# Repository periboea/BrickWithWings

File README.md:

# BrickWithWings

## What this thing is.

custom flight controller built around the STM32F446RETx microcontroller that currently has no wings and lives entirely rentfree in my head.

no specific target UAV in mind. primary purpose as a learning ground.

## Current status.

what exists: schematic of the power supply, microcontroller core, and ICM-42688-P motion sensor wired up with 0 ERC errors.

what will exist in the future (probably. hopefully): proper layout of components' footprints. routing. more features.

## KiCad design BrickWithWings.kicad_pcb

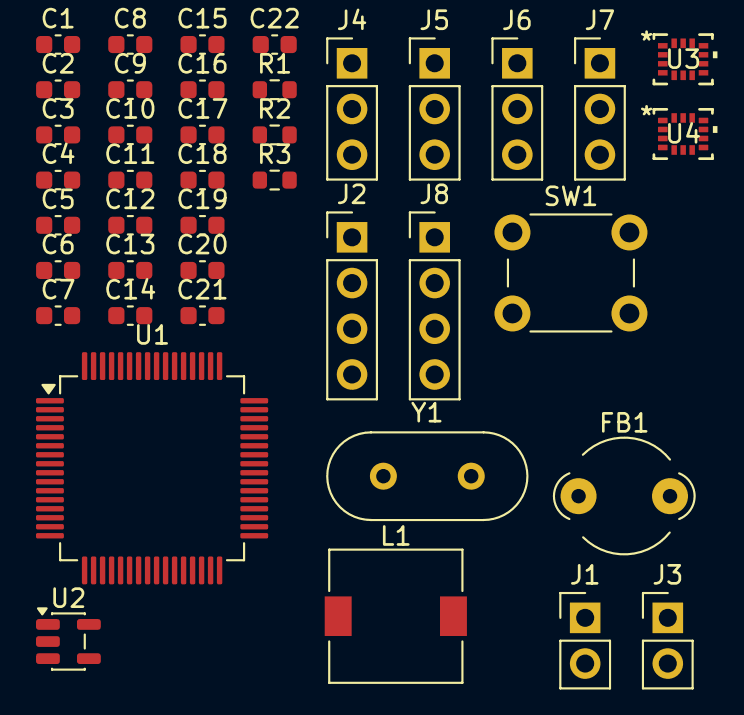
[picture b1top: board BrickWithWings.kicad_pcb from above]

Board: 2 copper layers, 41 parts (0 on the bottom side), 27 nets, no tracks yet.

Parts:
C1, C2, C3, C4, C6, C9, C15, C16: 100nF; C_0603_1608Metric
C5: 4.7uF; C_0603_1608Metric
C7, C12, C13: 1uF; C_0603_1608Metric
C8: 2.2muF; C_0603_1608Metric
C10, C11: 20pF; C_0603_1608Metric
C14: 10uF; C_0603_1608Metric
C17, C18: 22uF; C_0603_1608Metric
C19: 75pF; C_0603_1608Metric
C20: 0.1uF; C_0603_1608Metric
C21: 2.2uF; C_0603_1608Metric
C22: 10nF; C_0603_1608Metric
FB1: FerriteBead; LairdTech_28C0236-0JW-10
J1, J3: Conn_01x02_Pin; PinHeader_1x02_P2.54mm_Vertical
J2, J8: Conn_01x04_Pin; PinHeader_1x04_P2.54mm_Vertical
J4, J5, J6, J7: Conn_01x03_Pin; PinHeader_1x03_P2.54mm_Vertical
L1: 10uH; L_7.3x7.3_H4.5
R1: 10kΩ; R_0603_1608Metric
R2: 100kΩ; R_0603_1608Metric
R3: 13.3kΩ; R_0603_1608Metric
SW1: SW_Push; SW_PUSH_6mm
U1: STM32F446RETx; LQFP-64_10x10mm_P0.5mm
U2: AP2112K-3.3; SOT-23-5
U3: TPS54302; LGA14_2P5X3X0P91_TDK
U4: ICM-42688-P; LGA14_2P5X3X0P91_TDK
Y1: 8MHz; Crystal_HC49-U_Vertical

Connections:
+3V3: C1.1, C2.1, C3.1, C4.1, C5.1, C13.1, C20.1, C21.1, C22.1, FB1.1, J1.1, J2.1, U1.1 (VBAT), U1.19 (VDD), U1.32 (VDD), U1.48 (VDD), U1.64 (VDD), U2.5 (VOUT), U4.5 (VDDIO), U4.8 (VDD)
+5V: C12.1, C17.1, C18.1, C19.2, J8.1, L1.2, R2.2, U2.1 (VIN), U2.3 (EN)
/BOOT0: J1.2, R1.2, U1.60 (BOOT0)
/VDDA: C6.1, C7.1, FB1.2, U1.13 (VDDA)
GND: C1.2, C2.2, C3.2, C4.2, C5.2, C6.2, C7.2, C8.2, C9.1, C10.2, C11.2, C12.2, C13.2, C14.2, C15.2, C17.2, C18.2, C20.2, C21.2, C22.2, J2.4, J3.2, J4.3, J5.3, J6.3, J7.3, J8.4, R1.1, R3.1, SW1.1, U1.12 (VSSA), U1.18 (VSS), U1.31 (VSS), U1.47 (VSS), U1.63 (VSS), U2.2 (GND), U3.1 (GND), U4.6 (GND), Y1.2 (G)
GPIO_EXTI0: U1.14 (PA0), U4.4 (INT1/INT)
GPIO_EXTI1: U1.15 (PA1), U4.9 (INT2/FSYNC/CLKIN)
M1: J5.1, U1.58 (PB6)
M2: J4.1, U1.59 (PB7)
M3: J7.1, U1.61 (PB8)
M4: J6.1, U1.62 (PB9)
unnamed: C9.2, SW1.2, U1.7 (NRST)
unnamed: C8.1, U1.30 (VCAP_1)
unnamed: C16.1, U3.6 (BOOT)
unnamed: C19.1, R2.1, R3.2, U3.4 (FB)
unnamed: C16.2, L1.1, U3.2 (SW)
OSC_IN: C10.1, U1.5 (PH0), Y1.1
OSC_OUT: C11.1, U1.6 (PH1)
SPI1_MISO: U1.56 (PB4), U4.1 (AP_SDO/AP_AD0)
SPI1_MOSI: U1.57 (PB5), U4.14 (AP_SDA/AP_SDIO/AP_SDI)
SPI1_NSS: U1.20 (PA4), U4.12 (AP_CS)
SPI1_SCK: U1.21 (PA5), U4.13 (AP_SCL/AP_SCLK)
SWCLK: J2.3, U1.49 (PA14)
SWDIO: J2.2, U1.46 (PA13)
USART2_RX: J8.3, U1.17 (PA3)
USART2_TX: J8.2, U1.16 (PA2)
VBAT_IN: C14.1, C15.1, J3.1, U3.3 (VIN)
